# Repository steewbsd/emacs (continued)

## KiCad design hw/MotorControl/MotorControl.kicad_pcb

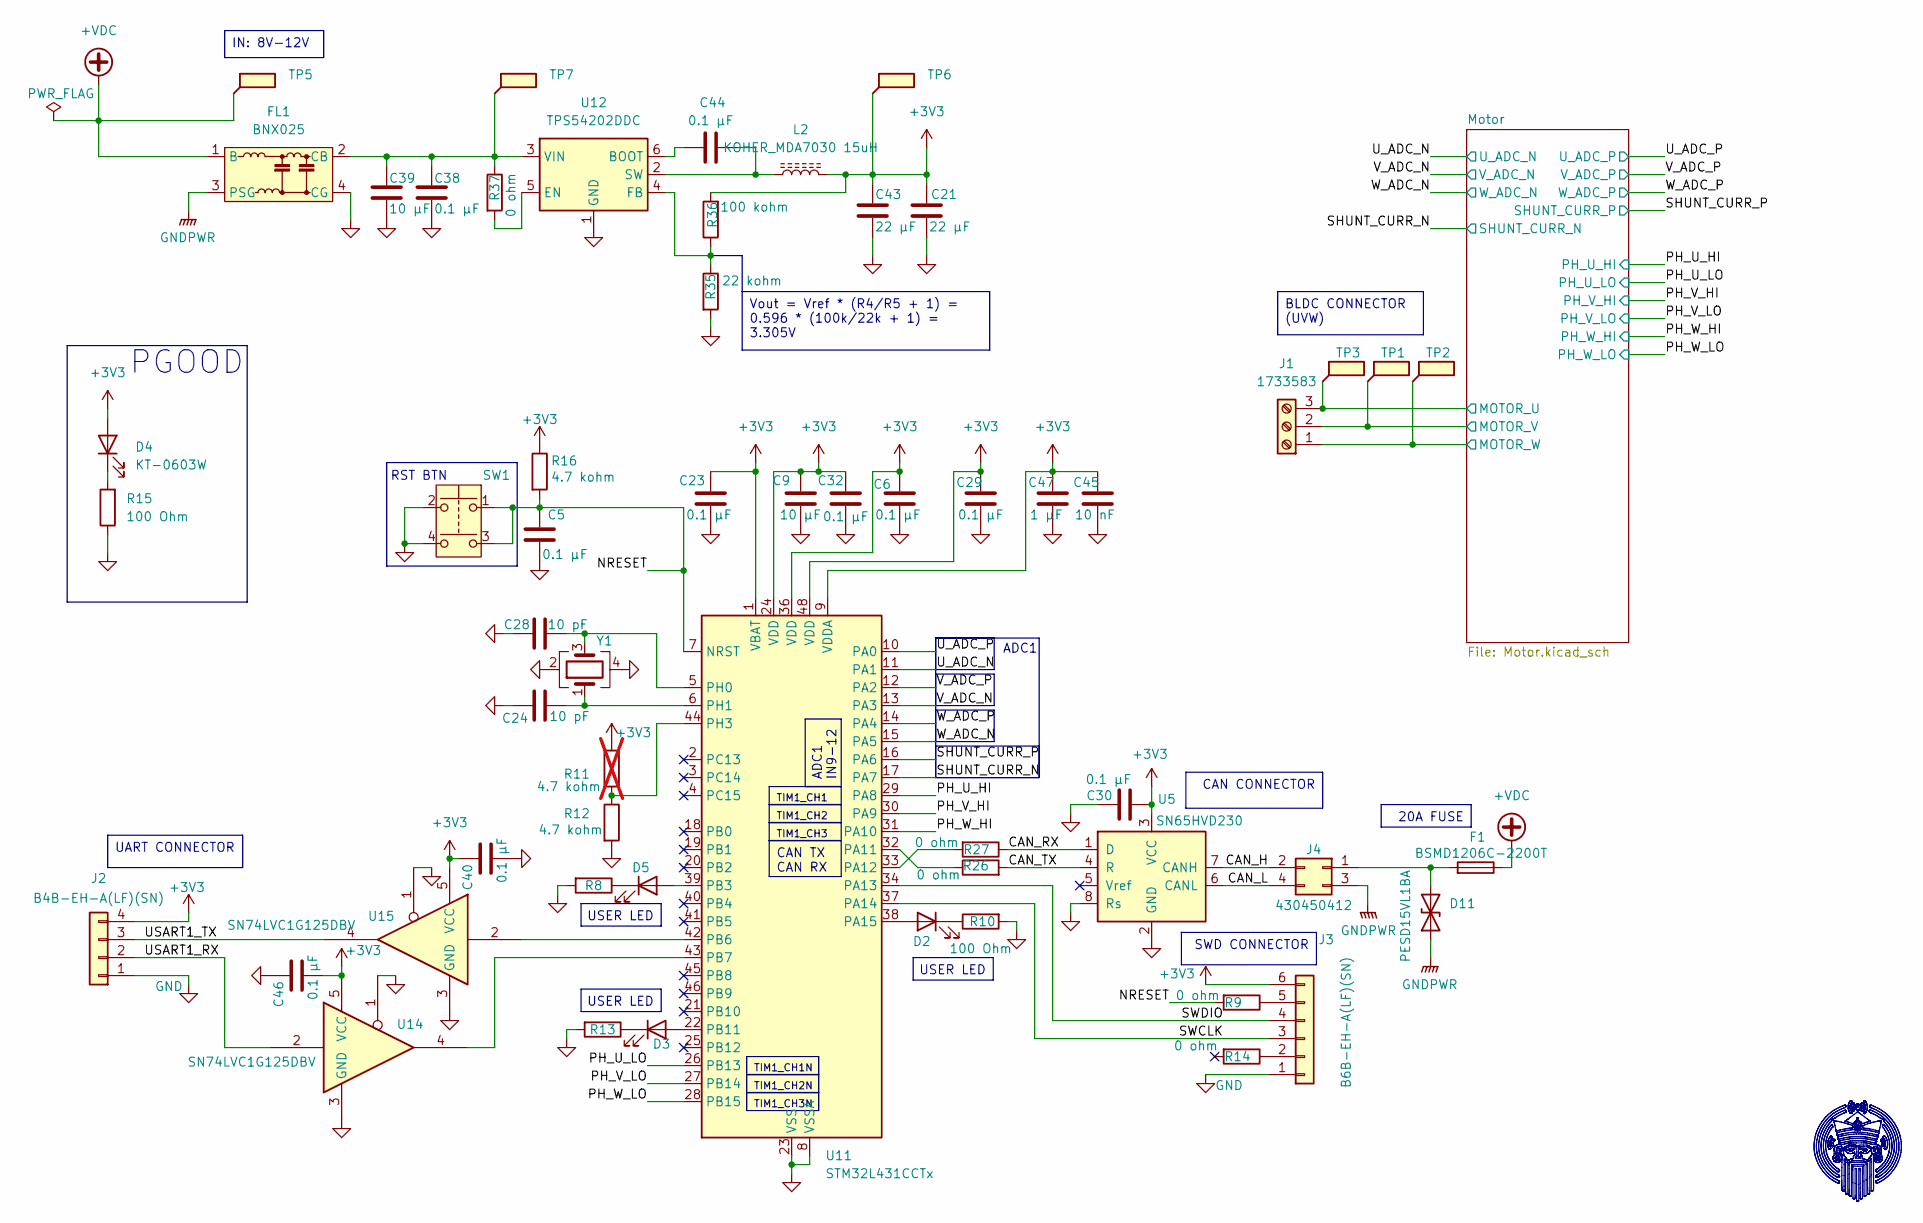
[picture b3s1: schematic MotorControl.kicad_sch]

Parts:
C5, C6, C23, C29, C30, C32, C38, C40, C44, C46: 0.1 µF; C_0805_2012Metric_Pad1.18x1.45mm_HandSolder; Rated Voltage 50V; Tolerance 10%
C9, C39: 10 µF; C_0805_2012Metric_Pad1.18x1.45mm_HandSolder; Rated Voltage 16V; Tolerance 10%
C21, C43: 22 µF; C_0805_2012Metric_Pad1.18x1.45mm_HandSolder; Rated Voltage 16V; Tolerance 20%
C24, C28: 10 pF; C_0805_2012Metric_Pad1.18x1.45mm_HandSolder; Rated Voltage 50V; Tolerance 0.25pF
C45: 10 nF; C_0805_2012Metric_Pad1.18x1.45mm_HandSolder; Rated Voltage 50V; Tolerance 10%
C47: 1 µF; C_0805_2012Metric_Pad1.18x1.45mm_HandSolder; Rated Voltage 25V; Tolerance 10%
D2, D3, D4, D5: KT-0603W; LED_0603_1608Metric_Pad1.05x0.95mm_HandSolder
D11: PESD15VL1BA; D_SOD-323_HandSoldering
F1: BSMD1206C-2200T; Fuse_1206_3216Metric_Pad1.42x1.75mm_HandSolder
FL1: BNX025; Filter_Murata_BNX025
J1: 1733583; TerminalBlock_Phoenix_MKDS-1,5-3-5.08_1x03_P5.08mm_Horizont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
J2: B4B-EH-A(LF)(SN); JST_EH_B4B-EH-A_1x04_P2.50mm_Vertical
J3: B6B-EH-A(LF)(SN); JST_EH_B6B-EH-A_1x06_P2.50mm_Vertical
J4: 430450412; Molex_Micro-Fit_3.0_43045-0412_2x02_P3.00mm_Vertical
L2: KOHER_MDA7030 15uH; L_KOHERelec_MDA7030
R8, R10, R13, R15: 100 Ohm; R_0603_1608Metric_Pad0.98x0.95mm_HandSolder
R9, R14, R26, R27, R37: 0 ohm; R_0603_1608Metric_Pad0.98x0.95mm_HandSolder; Tolerance Jumper
R11: 4.7 kohm; R_0603_1608Metric_Pad0.98x0.95mm_HandSolder; Tolerance 1%; not fitted
R12, R16: 4.7 kohm; R_0603_1608Metric_Pad0.98x0.95mm_HandSolder; Tolerance 1%
R35: 22 kohm; R_0603_1608Metric_Pad0.98x0.95mm_HandSolder; Tolerance 1%
R36: 100 kohm; R_0603_1608Metric_Pad0.98x0.95mm_HandSolder; Tolerance 1%
SW1: BTSA-N-P-1; SW_PUSH_6mm_H8mm
TP1, TP2, TP3, TP5, TP6, TP7: TestPoint_Flag; TestPoint_Plated_Hole_D2.0mm
U5: SN65HVD230; SOIC-8_3.9x4.9mm_P1.27mm
U11: STM32L431CCTx; LQFP-48_7x7mm_P0.5mm
U12: TPS54202DDC; SOT-23-6_Handsoldering
U14, U15: SN74LVC1G125DBV; SOT-23-5_HandSoldering
Y1: Crystal_GND24; Crystal_SMD_3225-4Pin_3.2x2.5mm_HandSoldering

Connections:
+3V3: C6.2, C9.1, C21.1, C23.2, C29.2, C30.1, C32.2, C40.2, C43.1, C45.2, C46.1, C47.2, D4.2 (A), J2.4, J3.6, L2.2, R11.1, R16.1, R36.2, TP6.1, U5.3 (VCC), U11.1 (VBAT), U11.9 (VDDA), U11.24 (VDD), U11.36 (VDD), U11.48 (VDD), U14.5 (VCC), U15.5 (VCC); also elsewhere on the board
+VDC: F1.1, FL1.1 (B), TP5.1; also elsewhere on the board
/CAN_H: J4.2, U5.7 (CANH)
/CAN_L: J4.4, U5.6 (CANL)
/CAN_RX: R27.1, U5.1 (D)
/CAN_TX: R26.2, U5.4 (R)
/Motor/MOTOR_U: J1.3, TP3.1; also elsewhere on the board
/Motor/MOTOR_V: J1.2, TP1.1; also elsewhere on the board
/Motor/MOTOR_W: J1.1, TP2.1; also elsewhere on the board
/NRESET: C5.1, R9.2, R16.2, SW1.1, SW1.3, U11.7 (NRST)
/PH_U_HI: U11.29 (PA8); also elsewhere on the board
/PH_U_LO: U11.26 (PB13); also elsewhere on the board
/PH_V_HI: U11.30 (PA9); also elsewhere on the board
/PH_V_LO: U11.27 (PB14); also elsewhere on the board
/PH_W_HI: U11.31 (PA10); also elsewhere on the board
/PH_W_LO: U11.28 (PB15); also elsewhere on the board
/SHUNT_CURR_N: U11.17 (PA7); also elsewhere on the board
/SHUNT_CURR_P: U11.16 (PA6); also elsewhere on the board
/SWCLK: J3.3, U11.37 (PA14)
/SWDIO: J3.4, U11.34 (PA13)
/USART1_RX: J2.2, U14.2
/USART1_TX: J2.3, U15.4
/U_ADC_N: U11.11 (PA1); also elsewhere on the board
/U_ADC_P: U11.10 (PA0); also elsewhere on the board
/V_ADC_N: U11.13 (PA3); also elsewhere on the board
/V_ADC_P: U11.12 (PA2); also elsewhere on the board
/W_ADC_N: U11.15 (PA5); also elsewhere on the board
/W_ADC_P: U11.14 (PA4); also elsewhere on the board
GND: C5.2, C6.1, C9.2, C21.2, C23.1, C24.1, C28.1, C29.1, C30.2, C32.1, C38.2, C39.2, C40.1, C43.2, C45.1, C46.2, C47.1, FL1.4 (CG), J2.1, J3.1, R8.2, R10.2, R12.2, R13.2, R15.1, R35.2, SW1.2, SW1.4, U5.2 (GND), U5.8 (Rs), U11.8 (VSSA), U11.23 (VSS), U11.35 (VSS), U11.47 (VSS), U12.1 (GND), U14.1, U14.3 (GND), U15.1, U15.3 (GND), Y1.2, Y1.4; also elsewhere on the board
GNDPWR: D11.1 (A1), FL1.3 (PSG), J4.3; also elsewhere on the board
unnamed: D2.2 (A), U11.38 (PA15)
unnamed: D2.1 (K), R10.1
unnamed: D3.2 (A), U11.22 (PB11)
unnamed: D3.1 (K), R13.1
unnamed: D4.1 (K), R15.2
unnamed: D5.2 (A), U11.39 (PB3)
unnamed: D5.1 (K), R8.1
unnamed: D11.2 (A2), F1.2, J4.1
unnamed: C38.1, C39.1, FL1.2 (CB), R37.1, TP7.1, U12.3 (VIN)
unnamed: J3.2, R14.1
unnamed: J3.5, R9.1
unnamed: R26.1, U11.32 (PA11)
unnamed: R27.2, U11.33 (PA12)
unnamed: U11.42 (PB6), U15.2
unnamed: U11.43 (PB7), U14.4
unnamed: C28.2, U11.5 (PH0), Y1.3
unnamed: C24.2, U11.6 (PH1), Y1.1
unnamed: R11.2, R12.1, U11.44 (PH3)
unnamed: C44.1, U12.6 (BOOT)
unnamed: R37.2, U12.5 (EN)
unnamed: R35.1, R36.1, U12.4 (FB)
unnamed: C44.2, L2.1, U12.2 (SW)

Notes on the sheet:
PGOOD
RST BTN
ADC1
USER LED
TIM1_CH1N
UART CONNECTOR
ADC1 IN9-12
TIM1_CH3N
20A FUSE
BLDC CONNECTOR (UVW)
CAN TX CAN RX
TIM1_CH2N
SWD CONNECTOR
CAN CONNECTOR
Vout = Vref * (R4/R5 + 1) = 0.596 * (100k/22k + 1) = 3.305V
TIM1_CH1
TIM1_CH3
TIM1_CH2
IN: 8V-12V

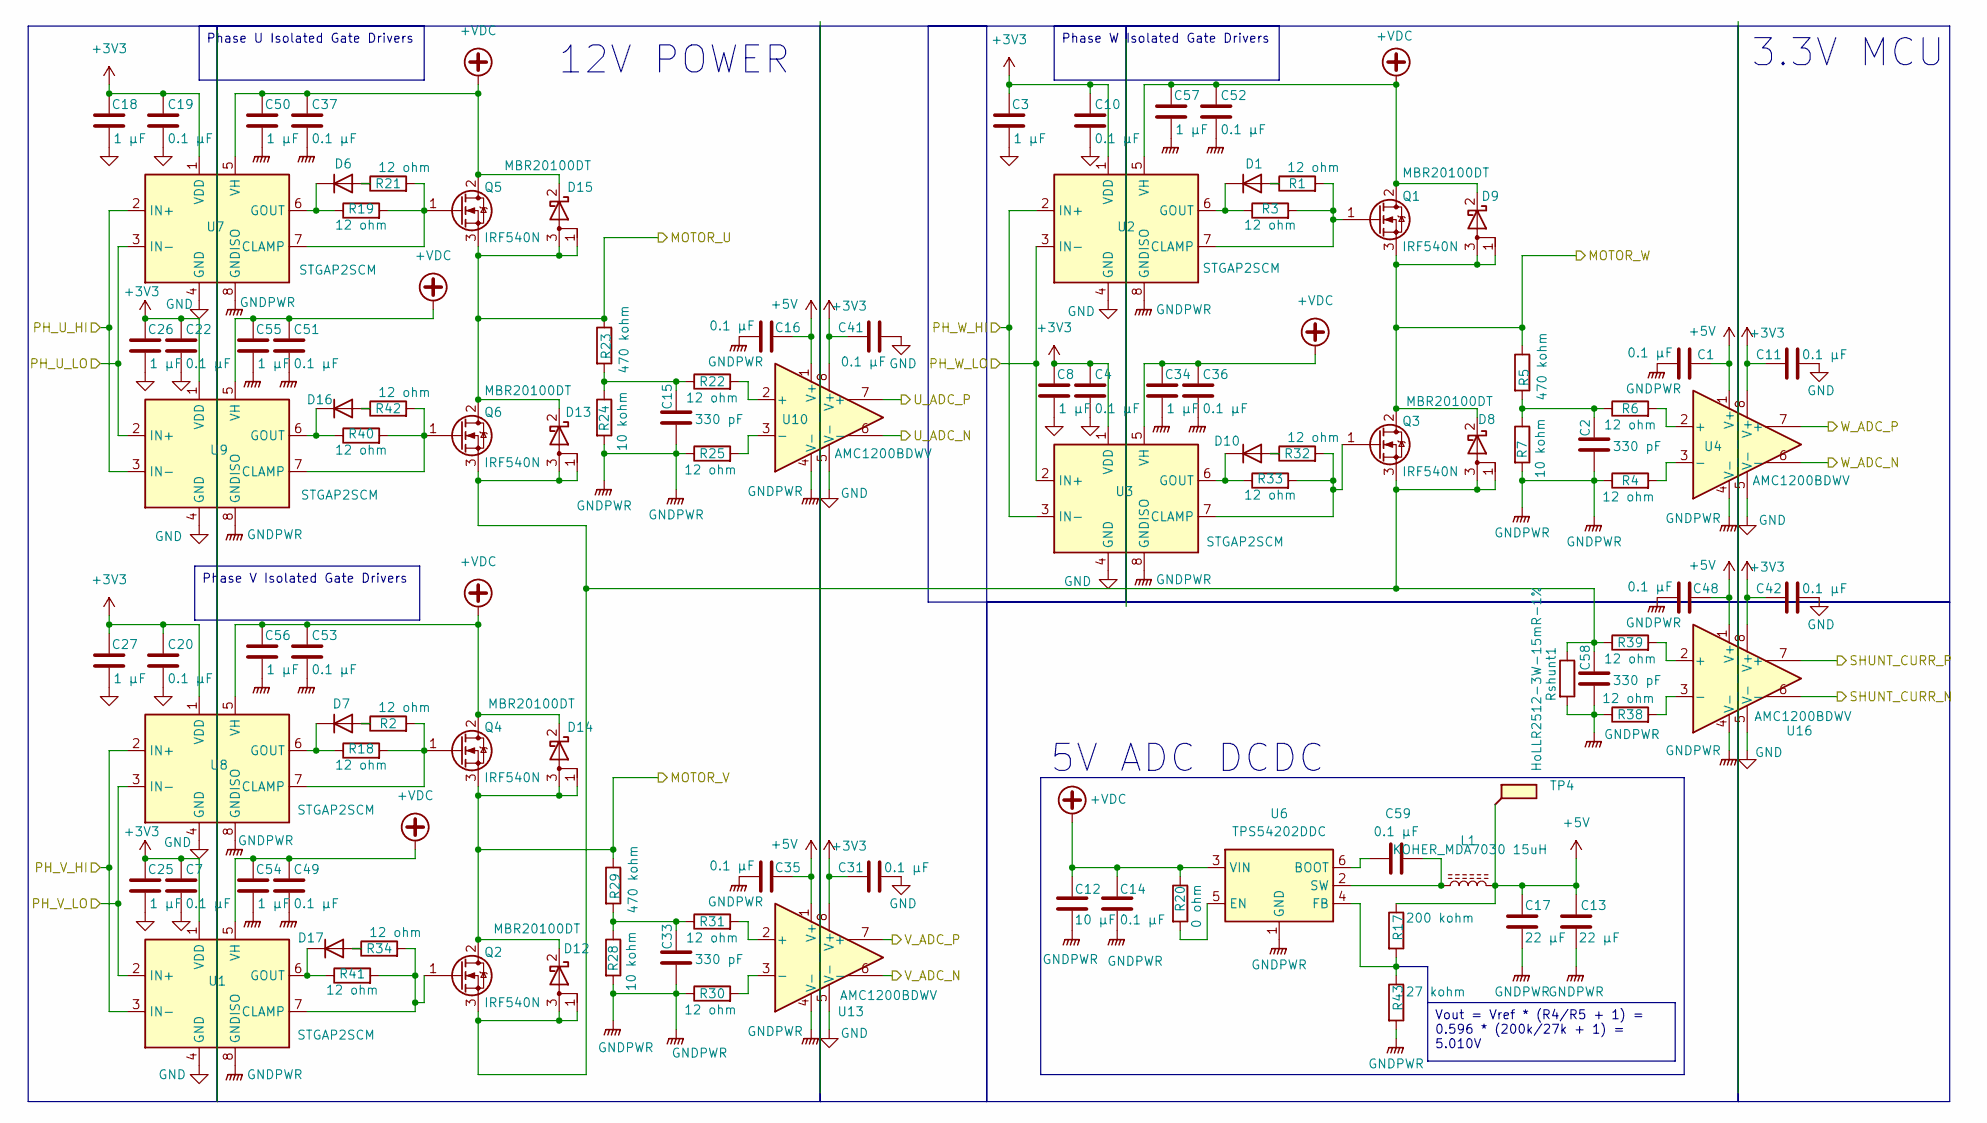
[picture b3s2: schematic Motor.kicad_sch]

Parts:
C1, C4, C7, C10, C11, C14, C16, C19, C20, C22, C31, C35, C36, C37, C41, C42, C48, C49, C51, C52, C53, C59: 0.1 µF; C_0805_2012Metric_Pad1.18x1.45mm_HandSolder; Rated Voltage 50V; Tolerance 10%
C2, C15, C33, C58: 330 pF; C_0805_2012Metric_Pad1.18x1.45mm_HandSolder; Rated Voltage 100V; Tolerance 5%
C3, C8, C18, C25, C26, C27, C34, C50, C54, C55, C56, C57: 1 µF; C_0805_2012Metric_Pad1.18x1.45mm_HandSolder; Rated Voltage 25V; Tolerance 10%
C12: 10 µF; C_0805_2012Metric_Pad1.18x1.45mm_HandSolder; Rated Voltage 16V; Tolerance 10%
C13, C17: 22 µF; C_0805_2012Metric_Pad1.18x1.45mm_HandSolder; Rated Voltage 16V; Tolerance 20%
D1, D6, D7, D10, D16, D17: 1N4148WS; D_SOD-323_HandSoldering
D8, D9, D12, D13, D14, D15: MBR20100DT; TO-252-2
L1: KOHER_MDA7030 15uH; L_KOHERelec_MDA7030
Q1, Q2, Q3, Q4, Q5, Q6: IRF540N; TO-220-3_Horizontal_TabDown
R1, R2, R3, R4, R6, R18, R19, R21, R22, R25, R30, R31, R32, R33, R34, R38, R39, R40, R41, R42: 12 ohm; R_0603_1608Metric_Pad0.98x0.95mm_HandSolder; Tolerance 1%
R5, R23, R29: 470 kohm; R_0603_1608Metric_Pad0.98x0.95mm_HandSolder; Tolerance 1%
R7, R24, R28: 10 kohm; R_0603_1608Metric_Pad0.98x0.95mm_HandSolder; Tolerance 1%
R17: 200 kohm; R_0603_1608Metric_Pad0.98x0.95mm_HandSolder; Tolerance 1%
R20: 0 ohm; R_0603_1608Metric_Pad0.98x0.95mm_HandSolder; Tolerance Jumper
R43: 27 kohm; R_0603_1608Metric_Pad0.98x0.95mm_HandSolder; Tolerance 1%
Rshunt1: HoLLR2512-3W-15mR-1%; R_2512_6332Metric_Pad1.40x3.35mm_HandSolder
TP4: TestPoint_Flag; TestPoint_Plated_Hole_D2.0mm
U1, U2, U3, U7, U8, U9: STGAP2SCM; SOIC-8_3.9x4.9mm_P1.27mm
U4, U10, U13, U16: AMC1200BDWV; SOIC-8_7.5x5.85mm_P1.27mm
U6: TPS54202DDC; SOT-23-6_Handsoldering

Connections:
+3V3: C3.1, C4.1, C7.1, C8.1, C10.1, C11.2, C18.1, C19.1, C20.1, C22.1, C25.1, C26.1, C27.1, C31.2, C41.2, C42.2, U1.1 (VDD), U2.1 (VDD), U3.1 (VDD), U4.8 (V+), U7.1 (VDD), U8.1 (VDD), U9.1 (VDD), U10.8 (V+), U13.8 (V+), U16.8 (V+); also elsewhere on the board
+5V: C1.2, C13.1, C16.2, C17.1, C35.2, C48.2, L1.2, R17.1, TP4.1, U4.1 (V+), U10.1 (V+), U13.1 (V+), U16.1 (V+)
+VDC: C12.1, C14.1, C34.1, C36.1, C37.1, C49.1, C50.1, C51.1, C52.1, C53.1, C54.1, C55.1, C56.1, C57.1, D9.2 (K), D14.2 (K), D15.2 (K), Q1.2 (D), Q4.2 (D), Q5.2 (D), R20.1, U1.5 (VH), U2.5 (VH), U3.5 (VH), U6.3 (VIN), U7.5 (VH), U8.5 (VH), U9.5 (VH); also elsewhere on the board
/Motor/MOTOR_U: D13.2 (K), D15.1 (A), D15.3 (A), Q5.3 (S), Q6.2 (D), R23.1; also elsewhere on the board
/Motor/MOTOR_V: D12.2 (K), D14.1 (A), D14.3 (A), Q2.2 (D), Q4.3 (S), R29.1; also elsewhere on the board
/Motor/MOTOR_W: D8.2 (K), D9.1 (A), D9.3 (A), Q1.3 (S), Q3.2 (D), R5.1; also elsewhere on the board
/PH_U_HI: U7.2 (IN+), U9.3 (IN-); also elsewhere on the board
/PH_U_LO: U7.3 (IN-), U9.2 (IN+); also elsewhere on the board
/PH_V_HI: U1.3 (IN-), U8.2 (IN+); also elsewhere on the board
/PH_V_LO: U1.2 (IN+), U8.3 (IN-); also elsewhere on the board
/PH_W_HI: U2.2 (IN+), U3.3 (IN-); also elsewhere on the board
/PH_W_LO: U2.3 (IN-), U3.2 (IN+); also elsewhere on the board
/SHUNT_CURR_N: U16.6 (-); also elsewhere on the board
/SHUNT_CURR_P: U16.7 (+); also elsewhere on the board
/U_ADC_N: U10.6 (-); also elsewhere on the board
/U_ADC_P: U10.7 (+); also elsewhere on the board
/V_ADC_N: U13.6 (-); also elsewhere on the board
/V_ADC_P: U13.7 (+); also elsewhere on the board
/W_ADC_N: U4.6 (-); also elsewhere on the board
/W_ADC_P: U4.7 (+); also elsewhere on the board
GND: C3.2, C4.2, C7.2, C8.2, C10.2, C11.1, C18.2, C19.2, C20.2, C22.2, C25.2, C26.2, C27.2, C31.1, C41.1, C42.1, U1.4 (GND), U2.4 (GND), U3.4 (GND), U4.5 (V-), U7.4 (GND), U8.4 (GND), U9.4 (GND), U10.5 (V-), U13.5 (V-), U16.5 (V-); also elsewhere on the board
GNDPWR: C1.1, C2.2, C12.2, C13.2, C14.2, C15.2, C16.1, C17.2, C33.2, C34.2, C35.1, C36.2, C37.2, C48.1, C49.2, C50.2, C51.2, C52.2, C53.2, C54.2, C55.2, C56.2, C57.2, C58.2, R4.1, R7.2, R24.2, R25.1, R28.2, R30.1, R38.1, R43.2, Rshunt1.2, U1.8 (GNDISO), U2.8 (GNDISO), U3.8 (GNDISO), U4.4 (V-), U6.1 (GND), U7.8 (GNDISO), U8.8 (GNDISO), U9.8 (GNDISO), U10.4 (V-), U13.4 (V-), U16.4 (V-); also elsewhere on the board
unnamed: C2.1, R5.2, R6.1, R7.1
unnamed: C15.1, R22.1, R23.2, R24.1
unnamed: C33.1, R28.1, R29.2, R31.1
unnamed: D1.2 (A), R1.1
unnamed: D1.1 (K), R3.1, U2.6 (GOUT)
unnamed: D6.2 (A), R21.1
unnamed: D6.1 (K), R19.1, U7.6 (GOUT)
unnamed: D7.2 (A), R2.1
unnamed: D7.1 (K), R18.1, U8.6 (GOUT)
unnamed: D10.2 (A), R32.1
unnamed: D10.1 (K), R33.1, U3.6 (GOUT)
unnamed: D16.2 (A), R42.1
unnamed: D16.1 (K), R40.1, U9.6 (GOUT)
unnamed: D17.2 (A), R34.1
unnamed: D17.1 (K), R41.1, U1.6 (GOUT)
unnamed: Q1.1 (G), R1.2, R3.2, U2.7 (CLAMP)
unnamed: Q2.1 (G), R34.2, R41.2, U1.7 (CLAMP)
unnamed: C58.1, D8.1 (A), D8.3 (A), D12.1 (A), D12.3 (A), D13.1 (A), D13.3 (A), Q2.3 (S), Q3.3 (S), Q6.3 (S), R39.1, Rshunt1.1
unnamed: Q3.1 (G), R32.2, R33.2, U3.7 (CLAMP)
unnamed: Q4.1 (G), R2.2, R18.2, U8.7 (CLAMP)
unnamed: Q5.1 (G), R19.2, R21.2, U7.7 (CLAMP)
unnamed: Q6.1 (G), R40.2, R42.2, U9.7 (CLAMP)
unnamed: R4.2, U4.3 (-)
unnamed: R6.2, U4.2 (+)
unnamed: R22.2, U10.2 (+)
unnamed: R25.2, U10.3 (-)
unnamed: R30.2, U13.3 (-)
unnamed: R31.2, U13.2 (+)
unnamed: R38.2, U16.3 (-)
unnamed: R39.2, U16.2 (+)
unnamed: C59.1, U6.6 (BOOT)
unnamed: R20.2, U6.5 (EN)
unnamed: R17.2, R43.1, U6.4 (FB)
unnamed: C59.2, L1.1, U6.2 (SW)

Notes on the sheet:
12V POWER
3.3V MCU
5V ADC DCDC
Phase W Isolated Gate Drivers
Phase V Isolated Gate Drivers
Phase U Isolated Gate Drivers
Vout = Vref * (R4/R5 + 1) = 0.596 * (200k/27k + 1) = 5.010V

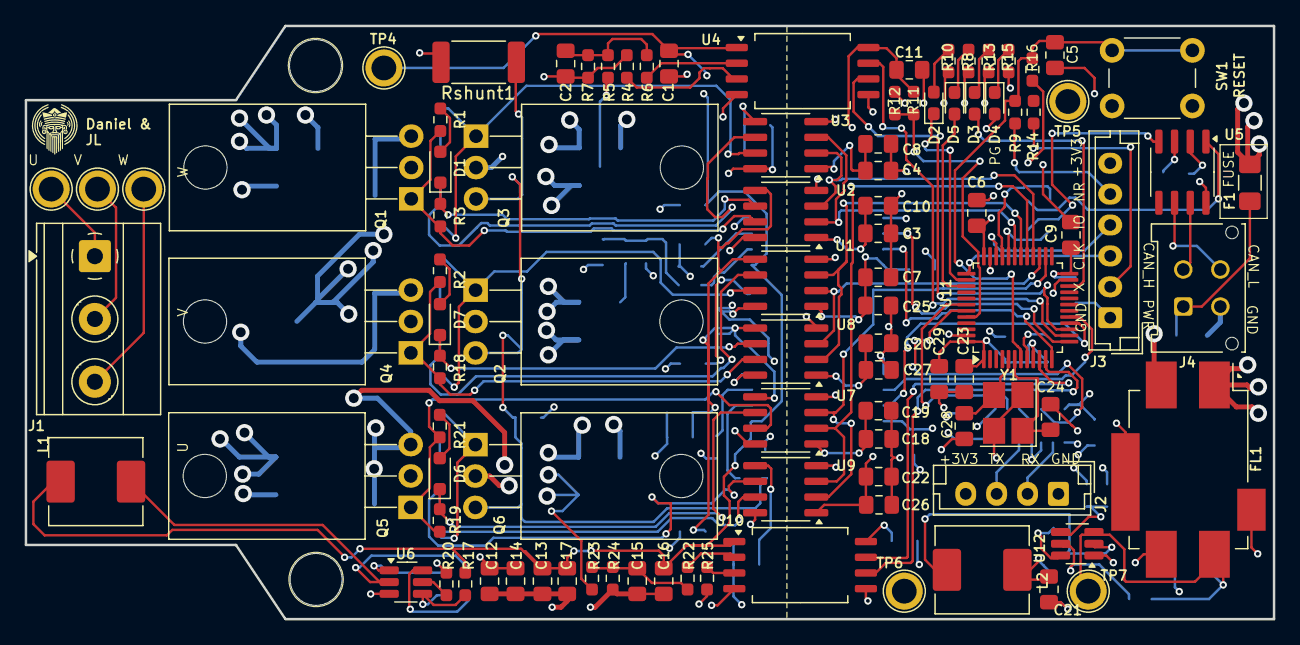
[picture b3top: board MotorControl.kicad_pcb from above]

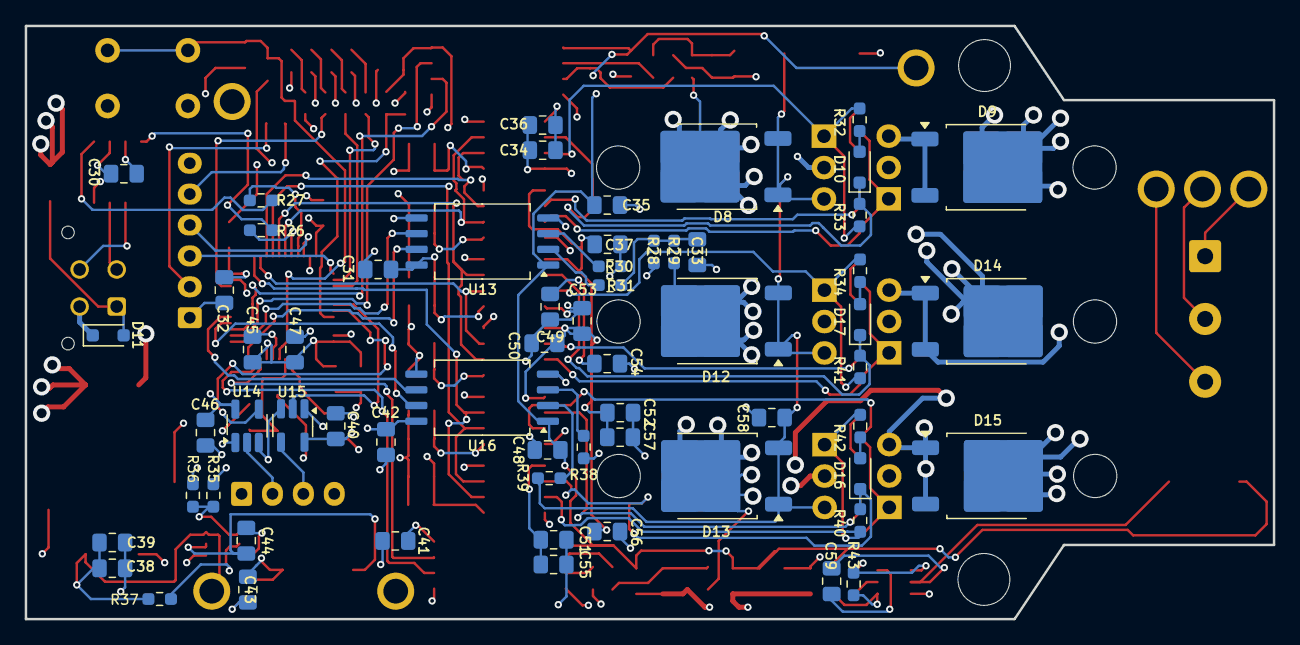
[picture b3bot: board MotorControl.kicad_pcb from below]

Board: 4 copper layers, 101.0 x 48.0 mm, 159 parts (62 on the bottom side), 87 nets.

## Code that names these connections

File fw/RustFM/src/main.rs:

#![no_std]
#![no_main]

use defmt::{trace};
use embassy_executor::Spawner;
use embassy_stm32::{
    exti::ExtiInput, gpio::{AnyPin, Level, Output, Speed}, i2c::{self, I2c, Master}, mode::Blocking, rcc::{self}, Config, Peri
};
use embassy_time::{Timer, Delay};
use {defmt_rtt as _, panic_probe as _};

use mpu6050_dmp::{sensor::Mpu6050};

#[embassy_executor::main]
async fn main(spawner: Spawner) {
    let mut config = Config::default();

    config.rcc.hse = Some(rcc::Hse {
        freq: embassy_stm32::time::Hertz(12_000_000),
        mode: rcc::HseMode::Oscillator,
    });
    let p = embassy_stm32::init(config);
    
    let iic = I2c::new_blocking(p.I2C1, p.PA9, p.PA10, i2c::Config::default());
    let _lsb_pin = Output::new(p.PA11, Level::Low, Speed::Low);

    let ok_pin = p.PC14;
    let fail_pin = p.PC15;
    let txpin = p.PA6;
    
    let _rxen = Output::new(p.PB0, Level::High, Speed::Low);
    let _txen = Output::new(p.PB1, Level::Low, Speed::Low);

    core::mem::forget(_rxen);
    core::mem::forget(_txen);
    core::mem::forget(_lsb_pin);

    let imu_int = ExtiInput::new(p.PA12, p.EXTI12, embassy_stm32::gpio::Pull::Down);
    
    spawner.spawn(transmit(txpin.into())).unwrap();
    spawner.spawn(read_mpu(iic, imu_int.into())).unwrap();

    spawner.spawn(status_leds(ok_pin.into())).unwrap();
    Timer::after_millis(500).await;
    spawner.spawn(status_leds(fail_pin.into())).unwrap();
    
}

#[embassy_executor::task(pool_size = 2)]
async fn status_leds(p: Peri<'static, AnyPin>) {
    let mut led = Output::new(p, Level::Low, Speed::Low);

    loop {
        led.set_high();
        Timer::after_millis(500).await;
        led.set_low();
        Timer::after_millis(500).await;
    }
}

#[embassy_executor::task]
async fn transmit(p: Peri<'static, AnyPin>) {
    let mut txpin = Output::new(p, Level::Low, Speed::VeryHigh);
    txpin.set_low();
    Timer::after_millis(1).await;
    txpin.set_high();
    Timer::after_millis(1).await;
    txpin.set_low();

    loop {
        txpin.toggle();
        Timer::after_millis(4).await;
    }
}


#[embassy_executor::task]
async fn read_mpu(iic: I2c<'static, Blocking, Master>, mut ext: ExtiInput<'static>) {
    let mpu = Mpu6050::new(iic, mpu6050_dmp::address::Address::default());
    let mut mpu = mpu.unwrap();
    mpu.initialize_dmp(&mut Delay).unwrap();
    mpu.enable_dmp().unwrap();
    mpu.set_clock_source(mpu6050_dmp::clock_source::ClockSource::Xgyro).unwrap();
    let mut fifo : [u8; 6] = [0; 6];
    mpu.interrupt_fifo_oflow_en().unwrap();
    mpu.enable_fifo().unwrap();
    mpu.interrupt_read_clear().unwrap();
    
    loop {
        ext.wait_for_rising_edge().await;
        trace!("Received new data");
        mpu.read_fifo(&mut fifo).unwrap();
        // let accel = mpu.gyro().unwrap();
        // trace!("X: {}, Y: {}, Z: {}" , accel.x(), accel.y(), accel.z());
        trace!("{}", fifo);
        mpu.interrupt_read_clear().unwrap();
    }
}
    

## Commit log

2022-03-14 Initial config
2022-03-31 clean config and get rid of use-package (and obsolete requires)
2022-03-31 add function to kill all buffers
2022-04-03 install packages if not present
2022-05-14 sort and cleanup init.el
2022-05-17 add some packages
2022-05-20 add screenshot
2025-02-27 feat: upload initial design with old name
2025-02-27 feat: add CNCs
2025-02-28 feat: start PCB
2025-02-28 bldc: start placement
2025-03-01 bldc: placement mostly done
2025-03-01 bldc: finish placement
2025-03-02 bldc: pre-routing commit
2025-03-02 bldc: pre branch
2025-04-16 before reroute
2025-04-16 half routed
2025-04-18 full route
2025-06-11 fmu: update power supply and other connections
2025-06-11 all: reorganize project
2025-06-12 add pdf outputs
2025-06-18 add NOR flash in FC
2025-06-20 final FC placement
2025-06-23 add power monitor
2025-06-24 preliminar design for battery power monitor, add sd card to fmu
2025-06-25 make fmu pcb more organized
2025-07-07 finish fmu routing
2025-07-07 FMU completed
2025-10-23 start working on firmware
2025-10-25 pre: cortex-m commit
2025-10-26 new config
2025-10-27 fixed version. mpu6050 3
2025-10-29 feat: working transmission
2025-11-01 First embassy version
2025-11-01 fmu-embassy: add mpu readings
